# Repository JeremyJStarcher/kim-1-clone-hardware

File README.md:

# kim-1-clone-hardware
Some hardware projects for the KIM-1 clone the PAL-1 and PAL-2

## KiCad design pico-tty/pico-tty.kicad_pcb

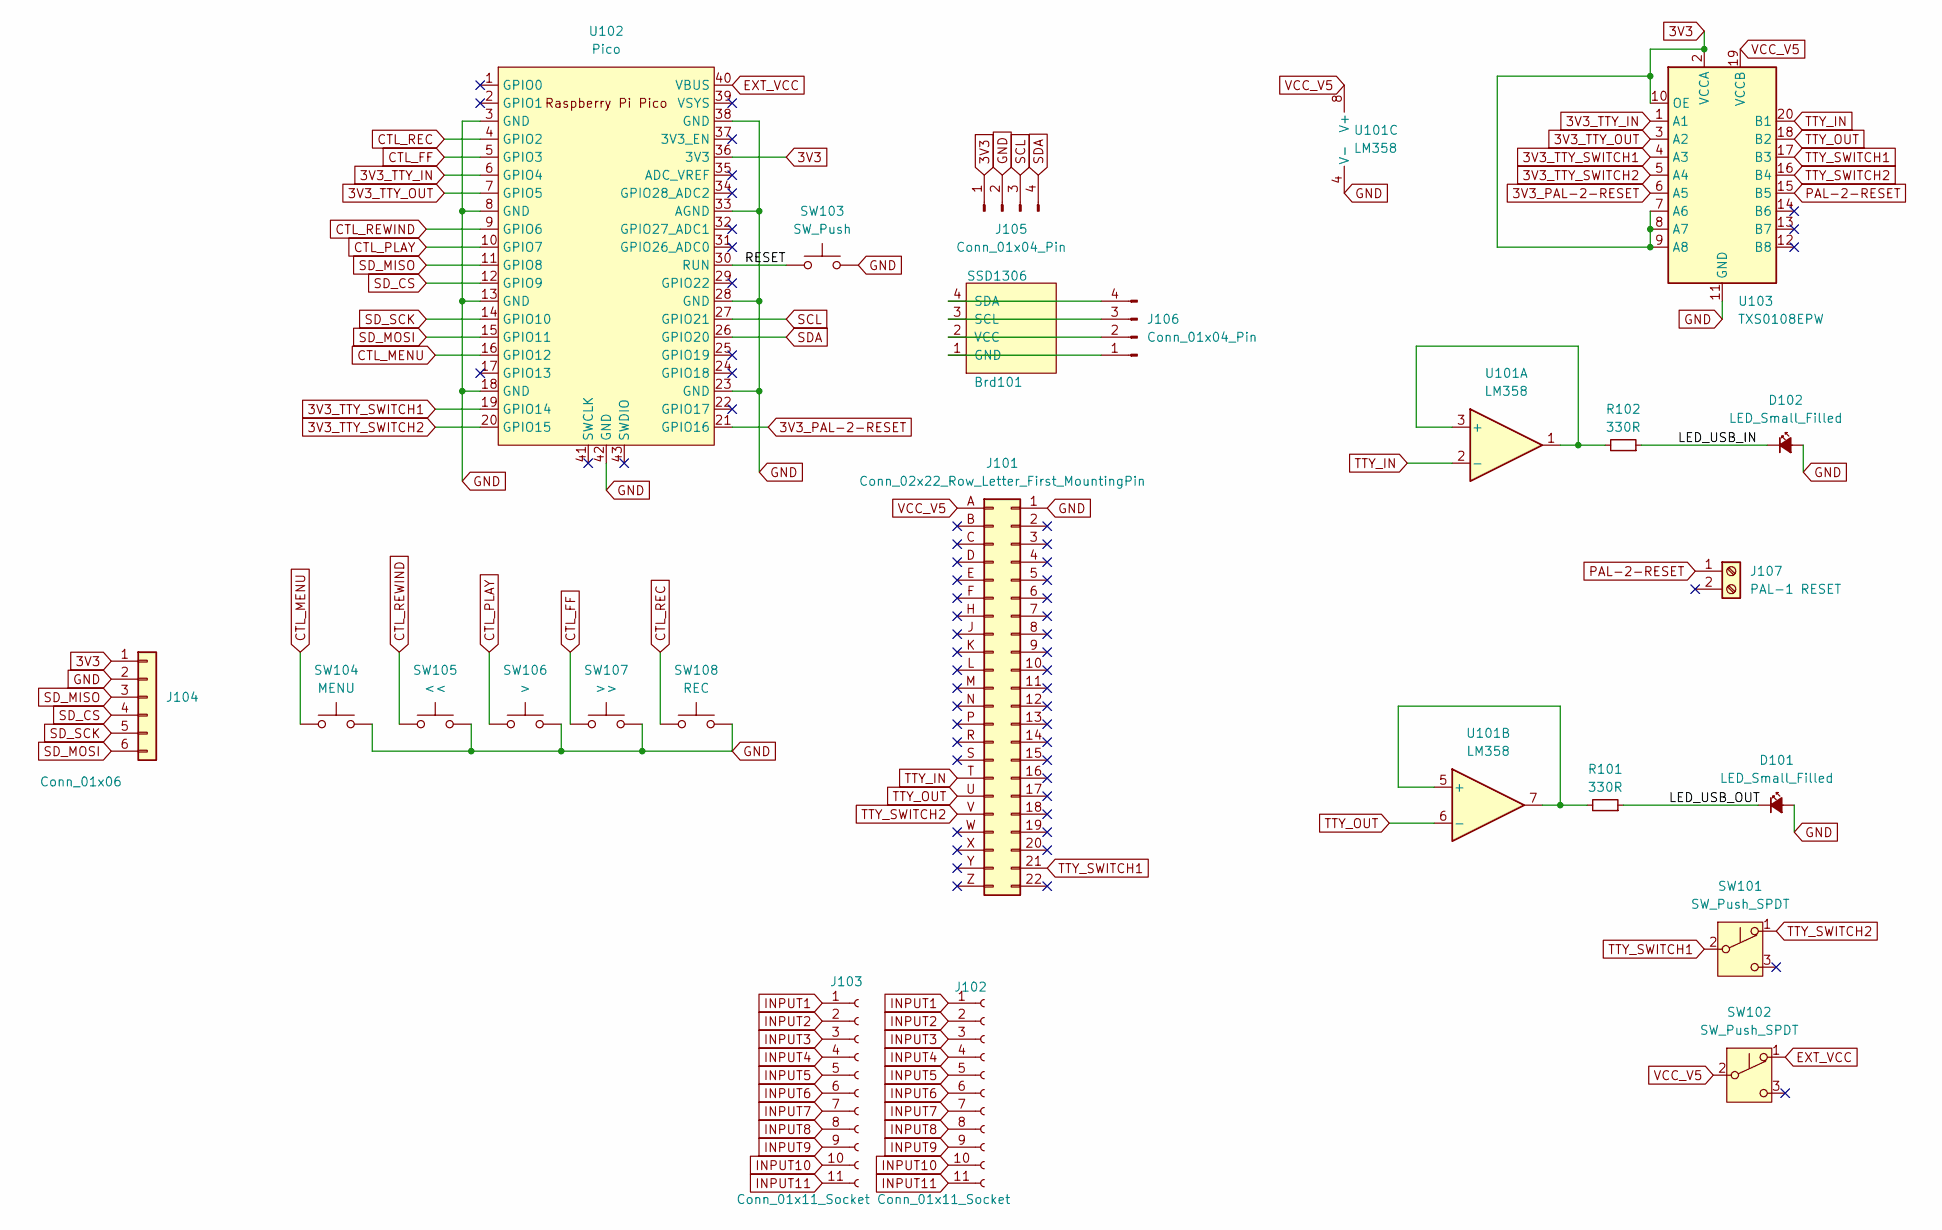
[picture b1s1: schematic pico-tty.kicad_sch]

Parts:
Brd101: SSD1306; 128x64OLED
D101, D102: LED_Small_Filled; LED_D5.0mm
J101: Conn_02x22_Row_Letter_First_MountingPin; IDC-Header_2x22_P2.54mm_Horizontal
J102: Conn_01x11_Socket; PinSocket_1x11_P2.54mm_Horizontal
J103: Conn_01x11_Socket; PinSocket_1x11_P2.54mm_Vertical
J104: Conn_01x06; PinSocket_1x06_P2.54mm_Vertical
J105, J106: Conn_01x04_Pin; PinHeader_1x04_P2.54mm_Vertical
J107: PAL-1 RESET; TerminalBlock_Xinya_XY308-2.54-2P_1x02_P2.54mm_Horizontal
R101, R102: 330R; R_Axial_DIN0204_L3.6mm_D1.6mm_P5.08mm_Horizontal
SW101, SW102: SW_Push_SPDT; switch
SW103: SW_Push; SW_PUSH_6mm
SW104: MENU; SW_PUSH_6mm
SW105: <<; SW_PUSH_6mm
SW106: >; SW_PUSH_6mm
SW107: >>; SW_PUSH_6mm
SW108: REC; SW_PUSH_6mm
U101: LM358; DIP-8_W7.62mm_LongPads
U102: Pico; RPi_PicoW_SMD_TH
U103: TXS0108EPW; TSSOP-20_4.4x6.5mm_P0.65mm; LCSC Part #' TXS0108EPW

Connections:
3V3: J104.1, J105.1, U102.36 (3V3), U103.2 (VCCA), U103.7 (A6), U103.8 (A7), U103.9 (A8), U103.10 (OE)
3V3_PAL-2-RESET: U102.21 (GPIO16), U103.6 (A5)
3V3_TTY_IN: U102.6 (GPIO4), U103.1 (A1)
3V3_TTY_OUT: U102.7 (GPIO5), U103.3 (A2)
3V3_TTY_SWITCH1: U102.19 (GPIO14), U103.4 (A3)
3V3_TTY_SWITCH2: U102.20 (GPIO15), U103.5 (A4)
/LED_USB_IN: D102.1 (K), R102.1
/LED_USB_OUT: D101.1 (K), R101.1
/RESET: SW103.1, U102.30 (RUN)
CTL_FF: SW107.1, U102.5 (GPIO3)
CTL_MENU: SW104.1, U102.16 (GPIO12)
CTL_PLAY: SW106.1, U102.10 (GPIO7)
CTL_REC: SW108.1, U102.4 (GPIO2)
CTL_REWIND: SW105.1, U102.9 (GPIO6)
EXT_VCC: SW102.1 (A), U102.40 (VBUS)
GND: D101.2 (A), D102.2 (A), J101.1 (Pin_b1), J104.2, J105.2, SW103.2, SW104.2, SW105.2, SW106.2, SW107.2, SW108.2, U101.4 (V-), U102.3 (GND), U102.8 (GND), U102.13 (GND), U102.18 (GND), U102.23 (GND), U102.28 (GND), U102.33 (AGND), U102.38 (GND), U102.42 (GND), U103.11 (GND)
INPUT1: J102.1, J103.1
INPUT2: J102.2, J103.2
INPUT3: J102.3, J103.3
INPUT4: J102.4, J103.4
INPUT5: J102.5, J103.5
INPUT6: J102.6, J103.6
INPUT7: J102.7, J103.7
INPUT8: J102.8, J103.8
INPUT9: J102.9, J103.9
INPUT10: J102.10, J103.10
INPUT11: J102.11, J103.11
unnamed: Brd101.1 (GND), J106.1
unnamed: Brd101.3 (SCL), J106.3
unnamed: Brd101.4 (SDA), J106.4
unnamed: Brd101.2 (VCC), J106.2
unnamed: R102.2, U101.1, U101.3 (+)
unnamed: R101.2, U101.5 (+), U101.7
PAL-2-RESET: J107.1, U103.15 (B5)
SCL: J105.3, U102.27 (GPIO21)
SDA: J105.4, U102.26 (GPIO20)
SD_CS: J104.4, U102.12 (GPIO9)
SD_MISO: J104.3, U102.11 (GPIO8)
SD_MOSI: J104.6, U102.15 (GPIO11)
SD_SCK: J104.5, U102.14 (GPIO10)
TTY_IN: J101.T (Pin_a16), U101.2 (-), U103.20 (B1)
TTY_OUT: J101.U (Pin_a17), U101.6 (-), U103.18 (B2)
TTY_SWITCH1: J101.21 (Pin_b21), SW101.2 (B), U103.17 (B3)
TTY_SWITCH2: J101.V (Pin_a18), SW101.1 (A), U103.16 (B4)
VCC_V5: J101.A (Pin_a1), SW102.2 (B), U101.8 (V+), U103.19 (VCCB)

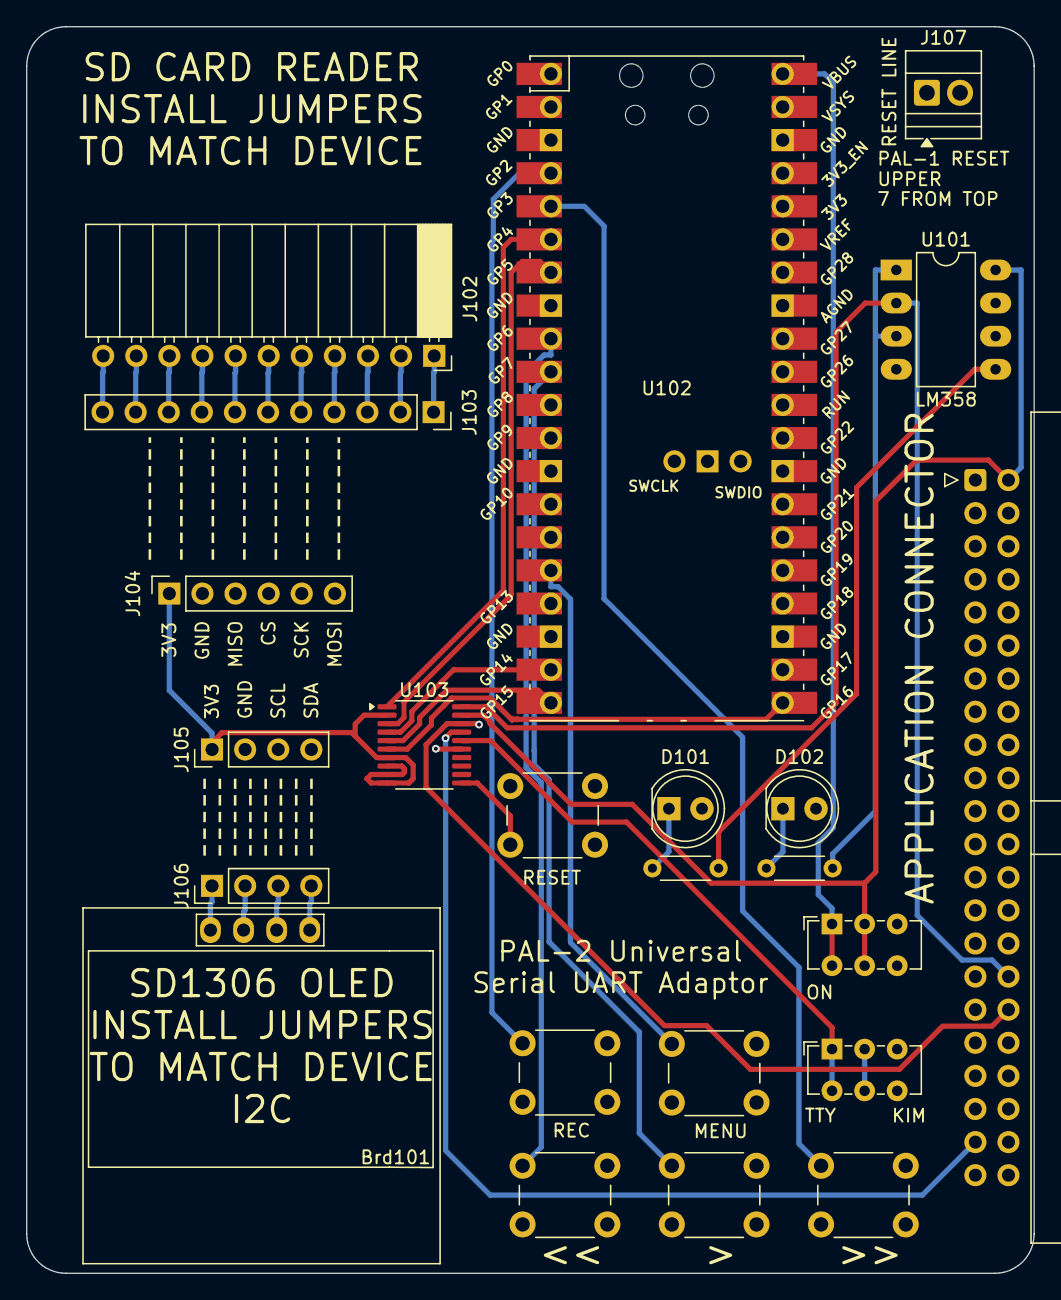
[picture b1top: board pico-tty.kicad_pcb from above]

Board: 4 copper layers, 77.3 x 95.7 mm, 23 parts (0 on the bottom side), 45 nets.

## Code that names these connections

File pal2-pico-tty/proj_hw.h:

#pragma once

#ifdef __cplusplus
extern "C"
{
#endif

#include "ssd1306.h"
    // #include "pico/stdlib.h"
    // #include "hardware/spi.h"
    // #include "hardware/i2c.h"
    // #include "hardware/pio.h"
    // #include "pico/cyw43_arch.h"
    // #include "hardware/uart.h"
    // #include "pico/binary_info.h"
    // #include "malloc.h"

    // SPI Defines
    // We are going to use SPI 0, and allocate it to the following GPIO pins
    // Pins can be changed, see the GPIO function select table in the datasheet for information on GPIO assignments

#define SPI_PORT spi1
#define PIN_MISO SD_MISO
#define PIN_CS SD_CS
#define PIN_SCK SD_SCK
#define PIN_MOSI SD_MOSI

// I2C defines
// This example will use I2C0 on GPIO8 (SDA) and GPIO9 (SCL) running at 400KHz.
// Pins can be changed, see the GPIO function select table in the datasheet for information on GPIO assignments
#define I2C_PORT i2c0
#define I2C_SDA 20
#define I2C_SCL 21

    static int BAUD_RATE = 9600;

#define PAL_RESET_GPIO 16
#define TTY_SWITCH2_OUTPUT 14
#define TTY_SWITCH1_INPUT 15
#define TTY_SWITCH1_DUP 18


#define PAL_UART uart0
#define PAL_UART_TX_GPIO 0
#define PAL_UART_RX_GPIO 1

    bool __no_inline_not_in_flash_func(get_bootsel_button)();
    void test_button(void);

    int scan_i2c_bus(void);
    void init_ssd1306(int addr, ssd1306_t *p);
    size_t get_largest_alloc_block_binary2(size_t low, size_t high);

    bool configure_hardware(void);

    void _error_blink(int count);
    void _toggle_led();
    void _toggle_led();
    void _set_led(bool flag);

#ifdef __cplusplus
}
#endif

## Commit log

2025-04-21 Initial file commit of example project
2025-04-21 sd-card reading working - at least the directories.
2025-04-21 Cleaned up code, got pico/pico_w detection working.
2025-04-21 Got graphics working.
2025-04-22 Added graphics and fixed submodule problems. All code is directly used.
2025-04-23 Now displaying the status on the OLED when possible.
2025-04-23 Displayed many of the status messages on the OLED
2025-04-23 Added in the SD card path and directory info.
2025-04-23 Pulled out a bunch of pico/pico-w specific code into its own file
2025-04-23 Enabled USB/UART passthrough
2025-04-24 Pin passthrough functioning correctly.
2025-04-24 Really commented the PIO code.
2025-05-03 Added a timeout for the USB handler.
2025-05-03 Updated build script to upload file automatically.
2025-05-03 Added frame buffer, but does not update screen yet.
2025-05-03 Frame buffer sent to ssd1306
2025-05-03 Changed boot status messages to use new tty code.
2025-05-04 Renamed jjs_init to switch_passthrough_init
2025-05-04 Cleaned up code/renamed functions/removed debugging delays.
2025-05-04 Moved the PCB over and button read code is now working.
2025-05-04 Added a scrolling select screen
2025-05-05 Got some nice typedefs in place now.
2025-05-05 The select list now works with big fonts
2025-05-05 Sub menus work.
2025-05-05 Debounce and repeat working so much smoother.
2025-05-05 Added a function to measure refresh time of the screen
2025-05-06 Removed 'color' parameter from draw functions. Reduced screen redraw in menu_select
2025-05-06 CHanged code to use a dynamic menu list for a file list
2025-05-07 Wrapped the menu in a wrapper to make malloc/free cleaner
2025-05-07 Reading directory and displaying it. Added bonus! Sorted directory list.
2025-05-07 File handling works.
    Directories can be fully navigated up and down.
    File selection works.
    File sent (though at full speed)
2025-05-07 Cleaned up progress counter.
2025-05-08 Code cleanup and PTP path adjusted for testing.
2025-05-10 Cleaned up some #DEFINEs with better options
2025-05-10 Lots of misc cleanup
    Wrapped boot messages in an DEBUG_MODE flag
    After sending a file, it returns to the top level.
    Bunch of files had source code reformatting
2025-05-14 Some cleanup and fixed the some of th I/O that got broken.
    Due to some refactoring without all hardware present to test
    the reset and TTY communication code stopped function.
2025-05-14 renamed tty_switch_passthrough to pal-io
2025-05-15 KIM/TTY toggle added. Reset still crude
2025-05-15 Refactored file upload and color-coded output for debugging.
2025-05-15 Added a USB timeout
2025-05-15 Added config settings and started switching over to them.
2025-05-15 Took advantage of the user config.
2025-05-15 Switched over to system_config.tty_mode
2025-05-16 Sending PTP files now puts the KIM into LOAD mode automatically.
    It also enables TTY mode if needed.
2025-05-16 Loading from cold boot, no terminal, fully functional.
2025-05-16 Crude bluetooth serial port enabled. Just chances ASCII case.
2025-05-17 uart bridge moved to core1. bt_stack requires core0
2025-05-17 PAL2 -> Sends to bluetooth receiver.
    The code gets a bit messy but I'm not sure how much that can be helped.
    Does not receive from bluetooth device yet but I don't expect that to be hard.
2025-05-17 A bunch of internal structural changes to begin supporting having TWO user IO streams.
    The USB serial connection and the bluetooth connection.
2025-05-17 Intern commit -- not functional
2025-05-17 Refactoring complete. I/O works from both USB and bluetooth
2025-05-18 Introduce u_puts and u_printf
2025-05-18 Did some more updating of u_* functions
2025-05-18 Cleaned up color stuff the best I could.
2025-05-18 Added handling of the new fields in the config.
2025-05-18 Resolved bluetooth lockups by putting request-to-send on an interrupt to force batching.
2025-05-18 Cleaned some some errors from missed violatile keywords
2025-05-18 Cleaned up a bunch of debug messages during init process.
2025-05-19 Added a dimmer and then poweroff when keyboard idle.
2025-05-19 Added comments to config file. Rename config file to config.ini
2025-05-19 Bluetooth connect and disconnect messages sent to the user.
2025-05-19 USB UART connected state tracked.
2025-05-20 Added pretty colors for system messages.
2025-05-20 Better display of upload results.
2025-05-20 Added color to the tty
2025-05-21 Resolved issue of BASIC uploads rebooting PAL.
2025-05-21 Have the SETTINGS menu appearing correctly.
2025-05-22 Have the configuration for BAUD working propertly
2025-05-22 Better menu handling.
2025-05-22 Switched to using the BT events instead of an outside interrupt.
2025-05-23 Starting different way to limit BT packet count
2025-05-23 Adjusted transfer batch size to match mtu. User keypresses get a priority.
2025-05-23 Added a script to open window at 80x25
2025-05-23 Cleaned up junk comments.
2025-05-24 Another round of anti-disconnect
2025-05-25 Tried more handling of time outs to see if they did anything.
2025-05-25 Set up a build to generate two different versions of the program.
2025-05-25 Got the USB-only mode working and, it seems, working well.
2025-05-25 A bunch of directory cleanup stuff. File re-arrangement
2025-05-25 And moved the PIO files
2025-05-25 Debugging cleanup.
2025-05-25 Wifi and telnet connection in place.
2025-05-25 Renamed ring buffer related things to bluetooth names to keep it sane.
2025-05-26 Added wifi/telnet support. LAGGY. Disconnects.
2025-05-26 Added scale and contrast for OLED screen to improve recordings.
2025-05-27 Fixed error that broke build. Static vars have to have a constant intitial value. Who knew :)
2025-05-28 Code should compile with the standard SDK or with the Pico extension
2025-05-29 Build system working better.
2025-05-30 Addin logging and debugging to test telnet
2025-06-04 More work to debug wifi and bluetooth
2025-06-04 Reverting to a known working bluetooth config
2025-06-05 Thank you Claude for finding bluetooth issues.
2025-06-05 Cleaned up build script.
2025-06-05 Dealt with some minor bugs on the telnet side.
2025-06-07 Wifi/bluetooth cleanup changes.
